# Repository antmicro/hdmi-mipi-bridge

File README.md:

# HDMI to MIPI CSI-2 Bridge

Copyright (c) 2017-2023 [Antmicro](https://www.antmicro.com)

## Overview
This repository contains the open hardware design files for Antmicro's HDMI-MIPI Bridge, which is a video accessory converting HDMI video stream into MIPI CSI-2 counterpart.
The conversion is performed using Toshiba [TC358743XBG](https://toshiba.semicon-storage.com/ap-en/semiconductor/product/interface-bridge-ics-for-mobile-peripheral-devices/hdmir-interface-bridge-ics/detail.TC358743XBG.html) HDMI interface bridge.
The board includes two independent conversion channels supporting up to two HDMI streams.

## Repository structure:

The main repository directory contains KiCad PCB project files, a [LICENSE](LICENSE), and a README.
The remaining files are stored in the following directories:

* `lib` - contains component libraries
* `doc` - contains generated schematics and other documentation
* `img` - contains graphics for this README

## Key features

* Two independent HDMI-MIPI CSI-2 conversion channels
* Converted MIPI CSI-2 data is exposed on two 4-lane interfaces
* Two assembly variants for regular HDMI and FFC connectors

## Supported platforms

The board exposes MIPI CSI-2 data on a unified 50-pin FFC connector which is electrically compatible with a variety of processing platforms designed by Antmicro.
Those platforms include: 

* [Jetson Nano / Xavier NX Baseboard](https://github.com/antmicro/jetson-nano-baseboard)
* [Jetson Orin NX Baseboard](https://github.com/antmicro/jetson-orin-baseboard)
* [Google Coral Baseboard](https://github.com/antmicro/google-coral-baseboard)
* [Apalis Smart Vision Baseboard](https://github.com/antmicro/apalis-smart-vision-baseboard)
* [TX2 Deep Learning Platform](https://github.com/antmicro/jetson-tx2-deep-learning-platform)

Please note that some additional work might be required to integrate this board with a particular host platform.
Antmicro’s services involve BSP development so you can hire us to make the necessary modifications.

## License

This project is licensed under the [Apache-2.0](LICENSE) license.

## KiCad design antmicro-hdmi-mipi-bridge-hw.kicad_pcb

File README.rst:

=========================
HDMI to MIPI CSI-2 bridge
=========================

Copyright (c) 2017-2021 `Antmicro <https://www.antmicro.com>`_

.. image:: Images/hdmi-mipi-bridge.jpg
   :scale: 40%

Overview
========

This repository contains the open hardware design files for Antmicro's HDMI-MIPI Bridge, which is a video accessory converting HDMI video stream into MIPI CSI-2 counterpart. The conversion is performed using Toshiba `TC358743XBG <https://toshiba.semicon-storage.com/ap-en/semiconductor/product/interface-bridge-ics-for-mobile-peripheral-devices/hdmir-interface-bridge-ics/detail.TC358743XBG.html>`_ HDMI interface bridge.
The board includes two independent conversion channels supporting up to two HDMI streams.

Repository structure:
---------------------

The main repository directory contains the Altium PCB project file, the Outjob file, LICENSE and README.
The remaining files are stored in the following directories:

* ``PCB`` -  contains all Altium design files
* ``Libraries`` - contains component libraries
* ``Documentation`` - contains selected files for device fabrication (schematic in PDF, BoM) generated from the Altium project
* ``Images`` - contains graphics for this README
* ``3DModels`` - contains files defining the mechanical model of the assembled board

Key features
============

* Two independent HDMI-MIPI CSI-2 conversion channels
* Converted MIPI CSI-2 data is exposed on two 4-lane interfaces
* Two assembly variants for regular HDMI and FFC connectors

The PCB project files were prepared in Altium Designer 14.1.

Supported platforms
===================

The board exposes MIPI CSI-2 data on a unified 50-pin FFC connector which is electrically compatible with a variety of processing platforms designed by Antmicro.
Those platforms include: 

* `Jetson Nano / Xavier NX Baseboard <https://github.com/antmicro/jetson-nano-baseboard>`_
* `Google Coral Baseboard <https://github.com/antmicro/google-coral-baseboard>`_
* `Apalis Smart Vision Baseboard <https://github.com/antmicro/apalis-smart-vision-baseboard>`_
* `TX2 Deep Learning Platform <https://github.com/antmicro/jetson-tx2-deep-learning-platform>`_

Please note that some additional work might be required to integrate this board with a particular host platform.
Antmicro’s services involve BSP development so you can hire us to make the necessary modifications.

License
=======

`Apache-2.0 <LICENSE>`_

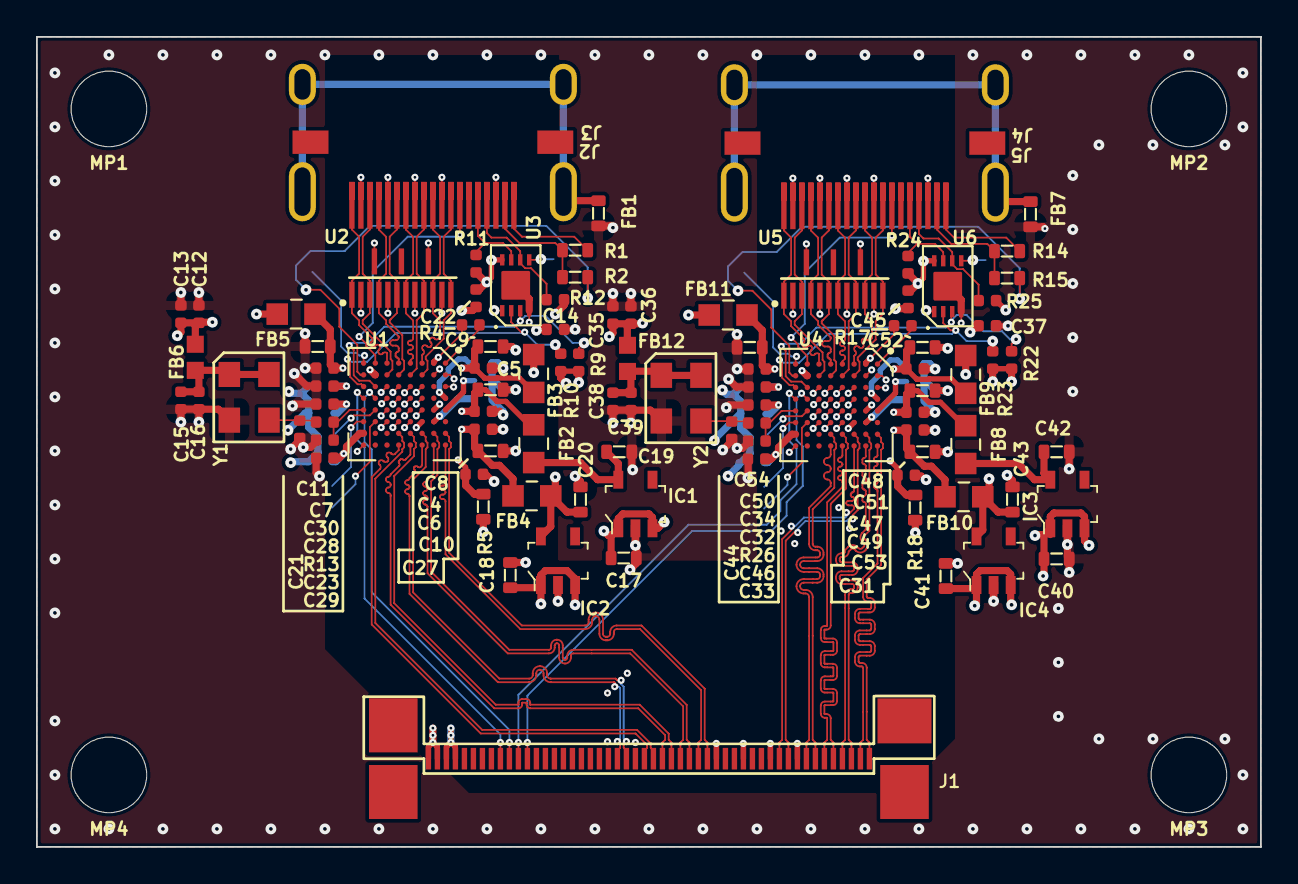
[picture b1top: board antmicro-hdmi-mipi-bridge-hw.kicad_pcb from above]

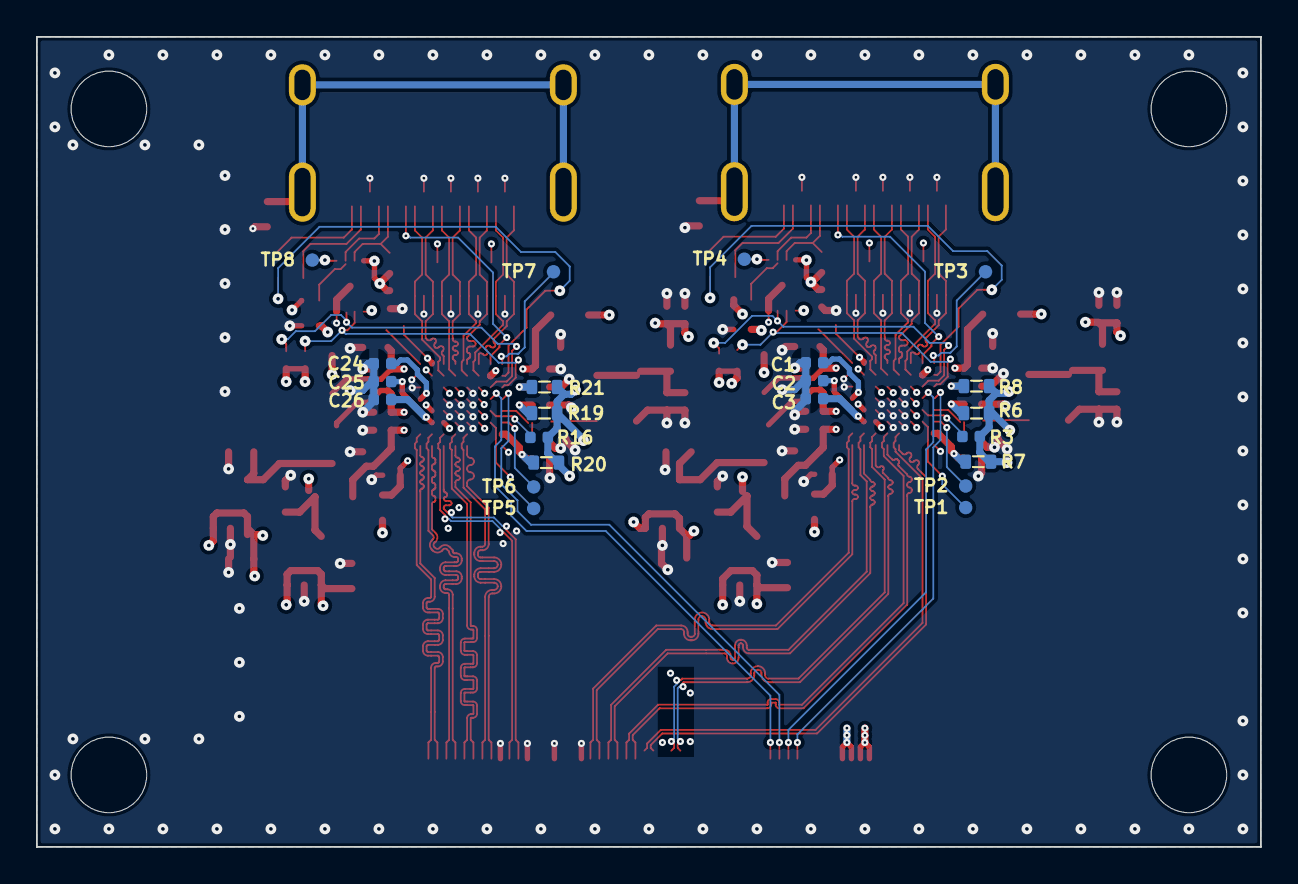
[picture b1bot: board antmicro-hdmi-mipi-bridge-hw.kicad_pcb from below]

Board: 4 copper layers, 68.0 x 45.0 mm, 121 parts (22 on the bottom side), 107 nets.

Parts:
C1, C2, C3, C12, C14, C15, C22, C24, C25, C26, C27, C28, C29, C30, C31, C32, C33, C34, C35, C37, C38, C45: C_100n_0402; 0402-cap
C4, C5, C6, C7, C47, C48, C49, C50: C_470p_0402; 0402-cap
C8, C9, C10, C11, C51, C52, C53, C54: C_4u7_0603; 0603-cap
C13, C16, C21, C23, C36, C39, C44, C46: C_47p_0402; 0402-cap
C17, C18, C19, C20, C40, C41, C42, C43: C_10u_0603; 0603-cap
FB1, FB7: BLM18SG121TN1D; 0603-res
FB2, FB3, FB4, FB5, FB8, FB9, FB10, FB11: 742792096; 0805-res
FB6, FB12: BLM18AG601SN1D; 0603
IC1, IC3: TLV73325PDBVT; SOT-23-5
IC2, IC4: TLV73312PDBVT; SOT-23-5
J1: WE_68715014522
J2, J4: 47151-1001
J3, J5: 5051101992
MP1, MP2, MP3, MP4: PCB_Mount_Hole_4.3_NPTH; mounting-hole-4.2mm-NPTH
R1, R2, R5, R6, R7, R8, R14, R15, R18, R19, R20, R21: R_0R_0603; 0603-res
R3, R9, R10, R11, R12, R16, R22, R23, R24, R25: R_10k_0402; 0402-res
R4, R17: R_2k_0402; 0402-res
R13, R26: R_22R_0402; 0402-res
TP1, TP2, TP3, TP4, TP5, TP6, TP7, TP8: TP_SMD_0_75MM; Testpoint_smd_0_75mm
U1, U4: TC358742XBG; BGA-64_8x8_6.0x6.0mm
U2, U5: TPD8S009DSMR; R-PDSO-N15
U3, U6: PCA9517ATP; SOT1069-2
Y1, Y2: 7C-27.000MBB-T; 7C-24.000MBB-T

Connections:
+3V3: C12.1, C13.1, C14.1, C17.1, C18.1, C35.1, C36.1, C37.1, C40.1, C41.1, FB6.1, FB12.1, IC1.1 (VIN), IC1.3 (EN), IC2.1 (VIN), IC2.3 (EN), IC3.1 (VIN), IC3.3 (EN), IC4.1 (VIN), IC4.3 (EN), J1.47, J1.48, R3.2, R6.2, R7.2, R8.2, R9.2, R10.2, R16.2, R19.2, R20.2, R21.2, R22.2, R23.2, U2.13 (VCC), U2.15 (VCC), U3.1 (Vref1), U5.13 (VCC), U5.15 (VCC), U6.1 (Vref1)
+5V: C22.1, C45.1, J1.49, J1.50, R11.2, R12.2, R24.2, R25.2, U3.8 (Vref2), U6.8 (Vref2)
/Channel 1/CH1_AVDD33: C30.1, R4.2, R8.1, U1.B1 (AVDD33), U1.F3 (AVDD33)
/Channel 1/CH1_REFCLK: C23.1, R13.2, U1.H5 (REFCLK)
/Channel 1/CH1_~RST: R3.1, U1.G5 (~RESET)
/Channel 1/DUMMY1: J2.14 (Utility), J3.14
/Channel 1/HDMI1_CEC: J2.13 (CEC), J3.13, U1.G1 (CEC)
/Channel 1/HDMI1_CLK_N: J2.12 (TMDS_Clock-), J3.12, U1.C2 (HDMIC_N), U2.12 (D3-)
/Channel 1/HDMI1_CLK_P: J2.10 (TMDS_Clock+), J3.10, U1.C1 (HDMIC_P), U2.10 (D3+)
/Channel 1/HDMI1_D0_N: J2.9 (TMDS_Data0-), J3.9, U1.D2 (HDMID0_N), U2.9 (D2-)
/Channel 1/HDMI1_D0_P: J2.7 (TMDS_Data0+), J3.7, U1.D1 (HDMID0_P), U2.7 (D2+)
/Channel 1/HDMI1_D1_N: J2.6 (TMDS_Data1-), J3.6, U1.E2 (HDMID1_N), U2.6 (D1-)
/Channel 1/HDMI1_D1_P: J2.4 (TMDS_Data1+), J3.4, U1.E1 (HDMID1_P), U2.4 (D1+)
/Channel 1/HDMI1_D2_N: J2.3 (TMDS_Data2-), J3.3, U1.F2 (HDMID2_N), U2.3 (D0-)
/Channel 1/HDMI1_D2_P: J2.1 (TMDS_Data2+), J3.1, U1.F1 (HDMID2_P), U2.1 (D0+)
/Channel 1/HDMI1_DDC_SCL: J2.15 (SCL), J3.15, R11.1, U3.7 (SCL2)
/Channel 1/HDMI1_DDC_SCL_3V3: R10.1, U1.H3 (DDC_SCL), U3.2 (SCL1)
/Channel 1/HDMI1_DDC_SDA: J2.16 (SDA), J3.16, R12.1, U3.6 (SDA2)
/Channel 1/HDMI1_DDC_SDA_3V3: R9.1, U1.G3 (DDC_SDA), U3.3 (SDA1)
/Channel 1/HDMI1_HPD: J2.19 (Hot_Plug_Detect), J3.19, R1.2
/Channel 1/HDMI1_HPDI: R2.2, U1.H2 (HPDI)
/Channel 1/HDMI1_HPDO: TP3.1, U1.H1 (HPDO)
/Channel 1/HDMI1_POWER: J2.18 (+5V_Power), J3.18, R1.1, R2.1
/Channel 2/CH2_AVDD33: C34.1, R17.2, R21.1, U4.B1 (AVDD33), U4.F3 (AVDD33)
/Channel 2/CH2_REFCLK: C46.1, R26.2, U4.H5 (REFCLK)
/Channel 2/CH2_~RST: R16.1, U4.G5 (~RESET)
/Channel 2/DUMMY2: J4.14 (Utility), J5.14
/Channel 2/HDMI2_CEC: J4.13 (CEC), J5.13, U4.G1 (CEC)
/Channel 2/HDMI2_CLK_N: J4.12 (TMDS_Clock-), J5.12, U4.C2 (HDMIC_N), U5.12 (D3-)
/Channel 2/HDMI2_CLK_P: J4.10 (TMDS_Clock+), J5.10, U4.C1 (HDMIC_P), U5.10 (D3+)
/Channel 2/HDMI2_D0_N: J4.9 (TMDS_Data0-), J5.9, U4.D2 (HDMID0_N), U5.9 (D2-)
/Channel 2/HDMI2_D0_P: J4.7 (TMDS_Data0+), J5.7, U4.D1 (HDMID0_P), U5.7 (D2+)
/Channel 2/HDMI2_D1_N: J4.6 (TMDS_Data1-), J5.6, U4.E2 (HDMID1_N), U5.6 (D1-)
/Channel 2/HDMI2_D1_P: J4.4 (TMDS_Data1+), J5.4, U4.E1 (HDMID1_P), U5.4 (D1+)
/Channel 2/HDMI2_D2_N: J4.3 (TMDS_Data2-), J5.3, U4.F2 (HDMID2_N), U5.3 (D0-)
/Channel 2/HDMI2_D2_P: J4.1 (TMDS_Data2+), J5.1, U4.F1 (HDMID2_P), U5.1 (D0+)
/Channel 2/HDMI2_DDC_SCL: J4.15 (SCL), J5.15, R24.1, U6.7 (SCL2)
/Channel 2/HDMI2_DDC_SCL_3V3: R23.1, U4.H3 (DDC_SCL), U6.2 (SCL1)
/Channel 2/HDMI2_DDC_SDA: J4.16 (SDA), J5.16, R25.1, U6.6 (SDA2)
/Channel 2/HDMI2_DDC_SDA_3V3: R22.1, U4.G3 (DDC_SDA), U6.3 (SDA1)
/Channel 2/HDMI2_HPD: J4.19 (Hot_Plug_Detect), J5.19, R14.2
/Channel 2/HDMI2_HPDI: R15.2, U4.H2 (HPDI)
/Channel 2/HDMI2_HPDO: TP7.1, U4.H1 (HPDO)
/Channel 2/HDMI2_POWER: J4.18 (+5V_Power), J5.18, R14.1, R15.1
CH1_1V2: C20.1, FB3.2, FB4.2, FB5.2, IC2.5 (VOUT)
CH1_2V5: C19.1, FB2.2, IC1.5 (VOUT)
CH2_1V2: C43.1, FB9.2, FB10.2, FB11.2, IC4.5 (VOUT)
CH2_2V5: C42.1, FB8.2, IC3.5 (VOUT)
CSI1_CLK_N: J1.28, U1.C7 (CSIC_N)
CSI1_CLK_P: J1.29, U1.C8 (CSIC_P)
CSI1_D1_N: J1.25, U1.E7 (CSID0_N)
CSI1_D1_P: J1.26, U1.E8 (CSID0_P)
CSI1_D2_N: J1.23, U1.D7 (CSID1_N)
CSI1_D2_P: J1.24, U1.D8 (CSID1_P)
CSI1_D3_N: J1.21, U1.B7 (CSID2_N)
CSI1_D3_P: J1.22, U1.B8 (CSID2_P)
CSI1_D4_N: J1.19, U1.A7 (CSID3_N)
CSI1_D4_P: J1.20, U1.A8 (CSID3_P)
CSI3_CLK_N: J1.10, U4.C7 (CSIC_N)
CSI3_CLK_P: J1.11, U4.C8 (CSIC_P)
CSI3_D1_N: J1.7, U4.E7 (CSID0_N)
CSI3_D1_P: J1.8, U4.E8 (CSID0_P)
CSI3_D2_N: J1.5, U4.D7 (CSID1_N)
CSI3_D2_P: J1.6, U4.D8 (CSID1_P)
CSI3_D3_N: J1.3, U4.B7 (CSID2_N)
CSI3_D3_P: J1.4, U4.B8 (CSID2_P)
CSI3_D4_N: J1.1, U4.A7 (CSID3_N)
CSI3_D4_P: J1.2, U4.A8 (CSID3_P)
GND: C1.2, C2.2, C3.2, C4.1, C5.1, C6.1, C7.1, C8.2, C9.2, C10.2, C11.2, C12.2, C13.2, C14.2, C15.2, C16.2, C17.2, C18.2, C19.2, C20.2, C21.2, C22.2, C23.2, C24.2, C25.2, C26.2, C27.2, C28.2, C29.2, C30.2, C31.2, C32.2, C33.2, C34.2, C35.2, C36.2, C37.2, C38.2, C39.2, C40.2, C41.2, C42.2, C43.2, C44.2, C45.2, C46.2, C47.1, C48.1, C49.1, C50.1, C51.2, C52.2, C53.2, C54.2, FB1.1, FB7.1, IC1.2 (GND), IC2.2 (GND), IC3.2 (GND), IC4.2 (GND), J1.9, J1.12, J1.15, J1.18, J2.2 (TMDS_Data2_Shield), J2.5 (TMDS_Data1_Shield), J2.8 (TMDS_Data0_Shield), J2.11 (TMDS_Clock_Shield), J2.17 (DDC/CEC_Ground), J3.2, J3.5, J3.8, J3.11, J3.17, J4.2 (TMDS_Data2_Shield), J4.5 (TMDS_Data1_Shield), J4.8 (TMDS_Data0_Shield), J4.11 (TMDS_Clock_Shield), J4.17 (DDC/CEC_Ground), J5.2, J5.5, J5.8, J5.11, J5.17, U1.A2 (GND), U1.A3 (VPGM), U1.C4 (GND), U1.C5 (GND), U1.D4 (GND), U1.D5 (GND), U1.D6 (GND), U1.E3 (GND), U1.E4 (GND), U1.E5 (TEST), U1.E6 (GND), U1.H8 (GND), U2.2 (GND), U2.5 (GND), U2.8 (GND), U2.11 (GND), U3.4 (GND), U3.EP, U4.A2 (GND), U4.A3 (VPGM), U4.C4 (GND), U4.C5 (GND), U4.D4 (GND), U4.D5 (GND), U4.D6 (GND), U4.E3 (GND), U4.E4 (GND), U4.E5 (TEST), U4.E6 (GND), U4.H8 (GND), U5.2 (GND), U5.5 (GND), U5.8 (GND), U5.11 (GND), U6.4 (GND), U6.EP, Y1.2 (GND), Y2.2 (GND)
I2C1_SCL: J1.42, U1.H4 (I2C_SCL)
I2C1_SDA: J1.41, U1.G4 (I2C_SDA)
I2C3_SCL: J1.40, U4.H4 (I2C_SCL)
I2C3_SDA: J1.39, U4.G4 (I2C_SDA)
unnamed: C1.1, U1.A4 (BIASDA)
unnamed: C2.1, U1.A5 (DAOUT)
unnamed: C3.1, U1.B6 (PCKIN)
unnamed: C4.2, C8.1, FB2.1, U1.B5 (AVDD25)
unnamed: C5.2, C9.1, FB3.1, U1.B2 (AVDD12), U1.D3 (AVDD12)
unnamed: C6.2, C10.1, FB4.1, U1.C6 (VDD_MIPI), U1.F6 (VDD_MIPI)
unnamed: C7.2, C11.1, FB5.1, R5.2, U1.G2 (VDDC1)
unnamed: C15.1, C16.1, FB6.2, Y1.1 (EN), Y1.4 (VDD)
unnamed: C21.1, R13.1, Y1.3 (OUT)
unnamed: C24.1, U4.A4 (BIASDA)
unnamed: C25.1, U4.A5 (DAOUT)
unnamed: C26.1, U4.B6 (PCKIN)
unnamed: C27.1, R5.1, U1.C3 (VDDC2), U1.F5 (VDDC2)
unnamed: C28.1, R6.1, U1.F4 (VDDIO1)
unnamed: C29.1, R7.1, U1.H7 (VDDIO2)
unnamed: C31.1, R18.1, U4.C3 (VDDC2), U4.F5 (VDDC2)
unnamed: C32.1, R19.1, U4.F4 (VDDIO1)
unnamed: C33.1, R20.1, U4.H7 (VDDIO2)
unnamed: C38.1, C39.1, FB12.2, Y2.1 (EN), Y2.4 (VDD)
unnamed: C44.1, R26.1, Y2.3 (OUT)
unnamed: C47.2, C51.1, FB8.1, U4.B5 (AVDD25)
unnamed: C48.2, C52.1, FB9.1, U4.B2 (AVDD12), U4.D3 (AVDD12)
unnamed: C49.2, C53.1, FB10.1, U4.C6 (VDD_MIPI), U4.F6 (VDD_MIPI)
unnamed: C50.2, C54.1, FB11.1, R18.2, U4.G2 (VDDC1)
unnamed: FB1.2, J2.S (SHIELD)
unnamed: FB7.2, J4.S (SHIELD)
unnamed: R4.1, U1.A1 (REXT)
unnamed: R17.1, U4.A1 (REXT)
unnamed: TP1.1, U1.G6 (EDID_SDA)
unnamed: TP2.1, U1.H6 (EDID_SCL)
unnamed: TP4.1, U3.5 (EN)
unnamed: TP5.1, U4.G6 (EDID_SDA)
unnamed: TP6.1, U4.H6 (EDID_SCL)
unnamed: TP8.1, U6.5 (EN)

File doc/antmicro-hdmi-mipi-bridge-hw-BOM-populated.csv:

"Reference","Quantity","Value","Footprint","Manufacturer","MPN"
"C1 C2 C3 C12 C14 C15 C22 C24 C25 C26 C27 C28 C29 C30 C31 C32 C33 C34 C35 C37 C38 C45","22","C_100n_0402","C_0402_1005Metric","Murata","GRM155R61H104KE14D"
"C4 C5 C6 C7 C47 C48 C49 C50","8","C_470p_0402","C_0402_1005Metric","Walsin","0402B471K250CT"
"C8 C9 C10 C11 C51 C52 C53 C54","8","C_4u7_0603","C_0603_1608Metric","TDK","C1608X5R1V475M080AC"
"C13 C16 C21 C23 C36 C39 C44 C46","8","C_47p_0402","C_0402_1005Metric","KEMET","C0402C470J5GACTU"
"C17 C18 C19 C20 C40 C41 C42 C43","8","C_10u_0603","C_0603_1608Metric","Murata","GRM188R61A106KE69D"
"FB1 FB7","2","FB_120Z_3A_Murata-BLM18SG_0603","FB_0603_1608Metric","Murata","BLM18SG121TN1D"
"FB2 FB3 FB4 FB5 FB8 FB9 FB10 FB11","8","FB_1kZ_0.8A_WE-CBF_0805","FB_0805_2012Metric","Würth Elektronik","742792096"
"FB6 FB12","2","FB_600Z_0.5A_Murata-BLM18AG_0603","FB_0603_1608Metric","Murata","BLM18AG601SN1D"
"IC1 IC3","2","TLV73325PDBVT","SOT-23-5","Texas Instruments","TLV73325PDBVT"
"IC2 IC4","2","TLV73312PDBVT","SOT-23-5","Texas Instruments","TLV73312PDBVT"
"J2 J4","2","HDMI-A_Molex_471511001","HDMI-A_Receptacle_Molex_471511001","Molex","471511001"
"J6","1","Conn_FFC_WE_68715014022","Conn_FFC_WE_68715014x22","Würth Elektronik","68715014022"
"N1","1","antmicro_logo","antmicro-logo_scaled_20mm_mask","",""
"N2","1","oshw_logo","OSHW-Logo_7.5x8mm_Mask","",""
"R1 R2 R5 R6 R7 R8 R14 R15 R18 R19 R20 R21","12","R_0R_0603","R_0603_1608Metric","Bourns","CR0603-J/-000ELF"
"R3 R9 R10 R11 R12 R16 R22 R23 R24 R25","10","R_10k_0402","R_0402_1005Metric","Bourns","CR0402-FX-1002GLF"
"R4 R17","2","R_2k_0402","R_0402_1005Metric","Bourns","CR0402-FX-2001GLF"
"R13 R26","2","R_22R_0402","R_0402_1005Metric","Bourns","CR0402-FX-22R0GLF"
"SP1 SP2 SP3 SP4","4","Spacer_Drill3.7mm_H6mm_9774060151R","Spacer_Drill3.7mm_H6mm_9774060151R","Würth Elektronik","9774060151R"
"U1 U4","2","TC358742XBG","BGA-64_8x8_6.0x6.0mm","Toshiba","TC358742XBG"
"U2 U5","2","TPD8S009DSMR","R-PDSO-N15","Texas Instruments","TPD8S009DSMR"
"U3 U6","2","PCA9517ATP","SOT1069-2","NXP","PCA9517ATP"
"Y1 Y2","2","Oscillator_27MHz_TXC_7C","Oscillator_SMD_TXC_7C_5x3.2x1.2mm","TXC","7C-27.000MBB-T"

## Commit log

2020-12-08 Add design files for release 1.2.1
2020-12-08 Update naming convention
2020-12-08 Update numbering
2020-12-08 Update schematics
2021-05-01 Notes added by 'git notes add'
2023-11-06 Add photo
2023-11-06 Ported schematics from altium
2023-11-06 Add initial README
2023-11-06 Update LICENSE
2023-11-06 Update schematic PDF
2023-11-06 Rearrange file structure
2023-11-06 Review HDMI-MIPI README
2023-11-06 Removed old altium files
2023-11-06 Updated components
2023-11-06 Fixed PCB logos
2023-11-06 Added PCB SHA
2023-11-06 Layout of the PCB
2023-11-06 Revision bump to 1.3.0
2023-11-06 Converted README to Markdown
2023-11-06 Small fixes to decoupling
2023-11-06 Changed mounting holes to stubs
2023-11-06 Update local library of components
2023-11-06 Change components to antmicro library ones
2023-11-06 Added logos
2023-11-06 Schematic cleanup
2023-11-06 Update PCB marking strings
2023-11-06 Introduce component standardization
2023-11-07 Add OHP assets
2024-04-19 [#58304] Migrate project to KiCad7
2024-04-19 [#58304] Perform globlib
2024-04-19 [#58304] Update symbols to global libs
2024-04-19 [#58304] WiP: Update footprints to global libs
2024-04-24 [#58304] Change J6 to Conn_FFC_WE_68715014x22_CUSTOM_FLIPPED
2024-04-24 [#58304] Clean DRC
2024-04-24 [#58304] Bump revision to 1.3.2
2024-04-25 [#58304] Revert flipping J6
2024-04-26 Update assets
2024-05-08 [#58304] Update ICs fileds visibility
2024-05-08 [#58304] Update PCA9517ATP symbol
2024-05-08 [#58304] kmake dnp
2024-05-08 [#58304] Remove loclib artifacts
2024-05-08 [#58304] Fix power flags orientation
2024-05-08 [#58304] Fix ERC
2024-05-08 [#58304] Fix DRC
2024-05-08 [#58304] Regenerate OHP assets
2024-06-05 [#58304] Allign power symbol labels
2024-06-05 [#58304] Update spacers footprint
2024-06-05 [#58304] Fix schematic after components lib rebase
2024-06-05 [#58304] Update OHP assets
2024-06-07 [#58304] Update MP from the library
